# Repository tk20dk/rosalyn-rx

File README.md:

# rosalyn-rx
Rosalyn LoRa receiver

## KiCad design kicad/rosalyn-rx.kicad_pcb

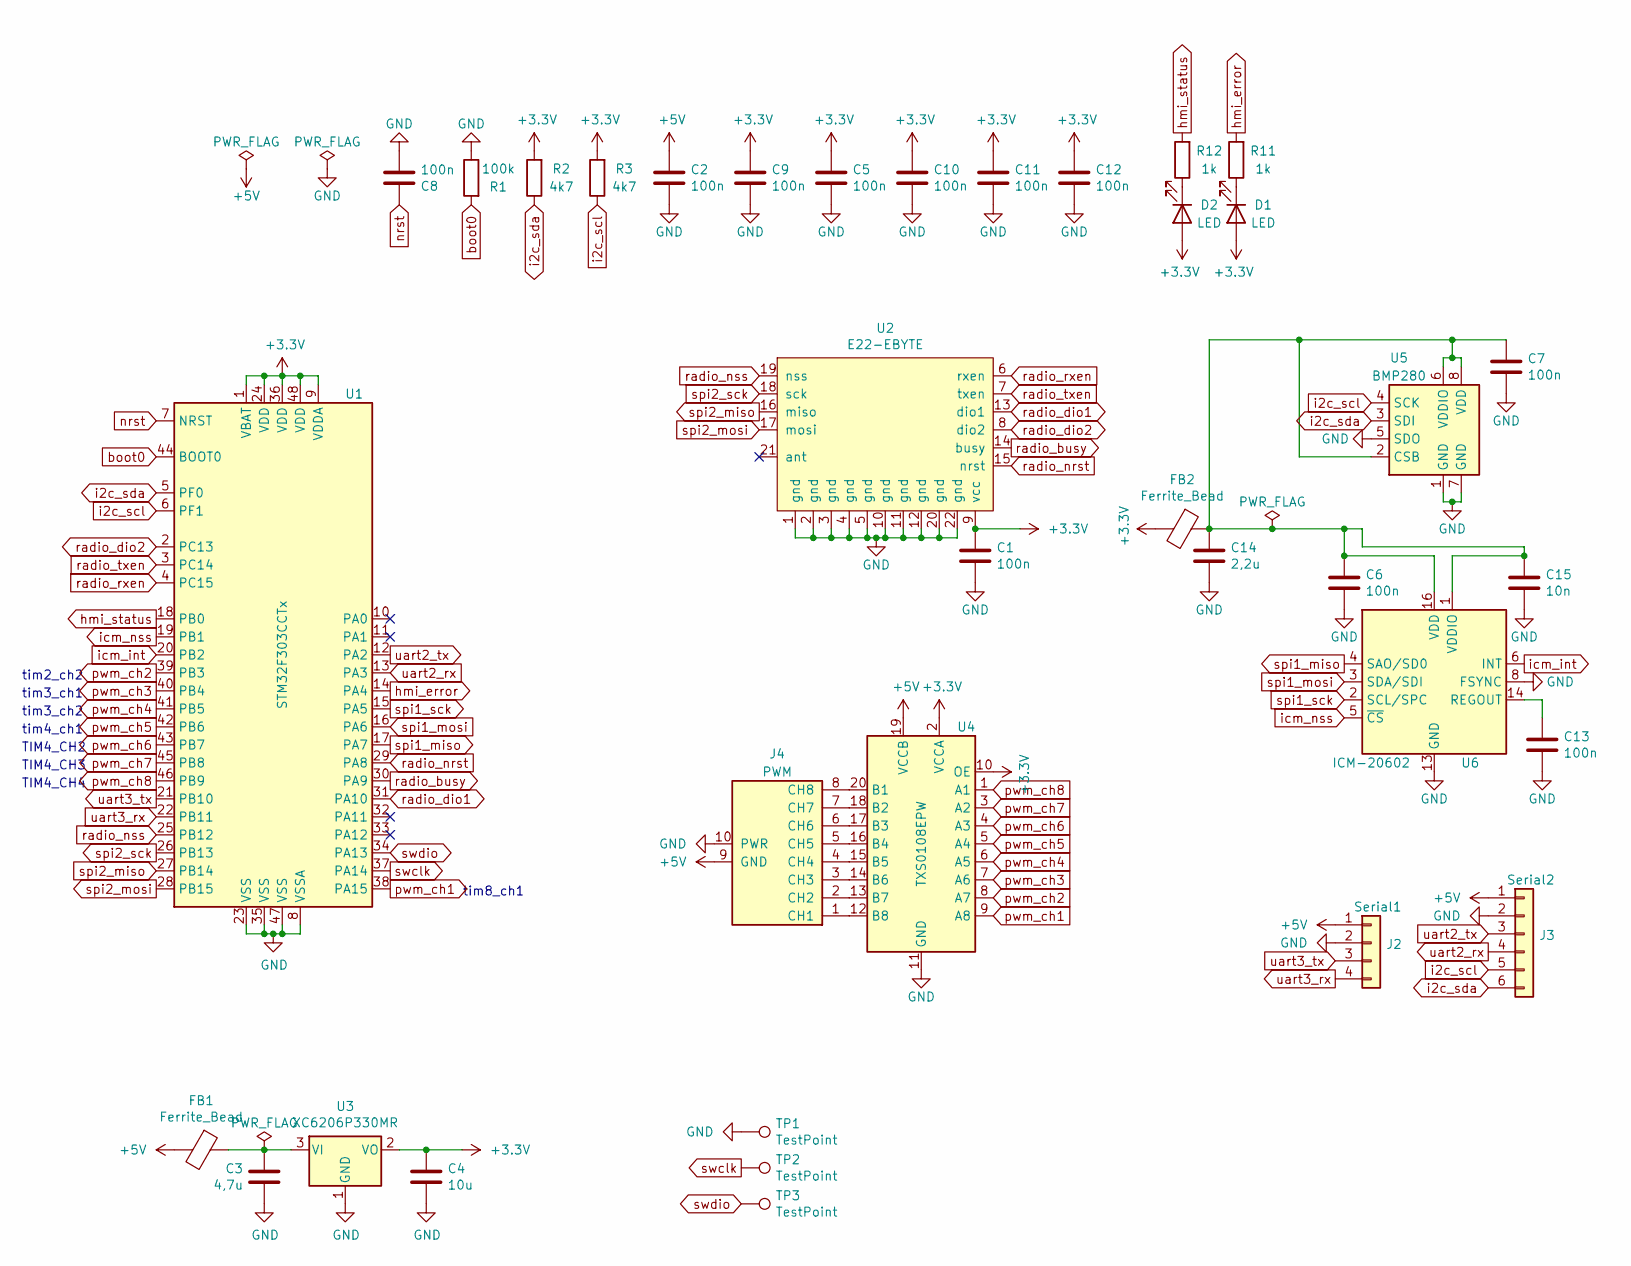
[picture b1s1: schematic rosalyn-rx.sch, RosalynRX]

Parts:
C1, C2, C5, C6, C7, C8, C9, C10, C11, C12, C13: 100n; C_0603_1608Metric
C3: 4,7u; C_0805_2012Metric
C4: 10u; C_0805_2012Metric
C14: 2,2u; C_0805_2012Metric
C15: 10n; C_0603_1608Metric
D1, D2: LED; LED_0603_1608Metric
FB1, FB2: Ferrite_Bead; L_0805_2012Metric
J2: Serial1; JST_SH_SM04B-SRSS-TB_1x04-1MP_P1.00mm_Horizontal
J3: Serial2; JST_SH_SM06B-SRSS-TB_1x06-1MP_P1.00mm_Horizontal
J4: PWM; PWM_3x08_P2.54mm_Vertical
R1: 100k; R_0603_1608Metric
R2, R3: 4k7; R_0603_1608Metric
R11, R12: 1k; R_0603_1608Metric
TP1, TP2, TP3: TestPoint; TestPoint_Pad_D1.0mm
U1: STM32F303CCTx; LQFP-48_7x7mm_P0.5mm
U2: E22-EBYTE
U3: XC6206P330MR; SOT-23
U4: TXS0108EPW; TSSOP-20_4.4x6.5mm_P0.65mm
U5: BMP280; Bosch_LGA-8_2x2.5mm_P0.65mm_ClockwisePinNumbering
U6: ICM-20602; LGA-16_3x3mm_P0.5mm_LayoutBorder3x5y

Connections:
+3V3: C1.1, C4.2, C5.1, C9.1, C10.1, C11.1, C12.1, D1.2 (A), D2.2 (A), FB2.2, R2.2, R3.2, U1.1 (VBAT), U1.9 (VDDA), U1.24 (VDD), U1.36 (VDD), U1.48 (VDD), U2.9 (vcc), U3.2 (VO), U4.2 (VCCA), U4.10 (OE)
+5V: C2.1, FB1.2, J2.1, J3.1, J4.9 (GND), U4.19 (VCCB)
GND: C1.2, C2.2, C3.1, C4.1, C5.2, C6.2, C7.2, C8.2, C9.2, C10.2, C11.2, C12.2, C13.2, C14.2, C15.2, J2.2, J3.2, J4.10 (PWR), R1.1, TP1.1, U1.8 (VSSA), U1.23 (VSS), U1.35 (VSS), U1.47 (VSS), U2.1 (gnd), U2.2 (gnd), U2.3 (gnd), U2.4 (gnd), U2.5 (gnd), U2.10 (gnd), U2.11 (gnd), U2.12 (gnd), U2.20 (gnd), U2.22 (gnd), U3.1 (GND), U4.11 (GND), U5.1 (GND), U5.5 (SDO), U5.7 (GND), U6.8 (FSYNC), U6.9 (GND), U6.10 (GND), U6.11 (GND), U6.12 (GND), U6.13 (GND), U6.15 (GND)
unnamed: C3.2, FB1.1, U3.3 (VI)
unnamed: C13.1, U6.14 (REGOUT)
unnamed: C6.1, C7.1, C14.1, C15.1, FB2.1, U5.2 (CSB), U5.6 (VDDIO), U5.8 (VDD), U6.1 (VDDIO), U6.16 (VDD)
unnamed: D1.1 (K), R11.1
unnamed: D2.1 (K), R12.1
unnamed: J4.1 (CH1), U4.12 (B8)
unnamed: J4.2 (CH2), U4.13 (B7)
unnamed: J4.3 (CH3), U4.14 (B6)
unnamed: J4.4 (CH4), U4.15 (B5)
unnamed: J4.5 (CH5), U4.16 (B4)
unnamed: J4.6 (CH6), U4.17 (B3)
unnamed: J4.7 (CH7), U4.18 (B2)
unnamed: J4.8 (CH8), U4.20 (B1)
boot0: R1.2, U1.44 (BOOT0)
hmi_error: R11.2, U1.14 (PA4)
hmi_status: R12.2, U1.18 (PB0)
i2c_scl: J3.5, R3.1, U1.6 (PF1), U5.4 (SCK)
i2c_sda: J3.6, R2.1, U1.5 (PF0), U5.3 (SDI)
icm_int: U1.20 (PB2), U6.6 (INT)
icm_nss: U1.19 (PB1), U6.5 (~CS)
nrst: C8.1, U1.7 (NRST)
pwm_ch1: U1.38 (PA15), U4.9 (A8)
pwm_ch2: U1.39 (PB3), U4.8 (A7)
pwm_ch3: U1.40 (PB4), U4.7 (A6)
pwm_ch4: U1.41 (PB5), U4.6 (A5)
pwm_ch5: U1.42 (PB6), U4.5 (A4)
pwm_ch6: U1.43 (PB7), U4.4 (A3)
pwm_ch7: U1.45 (PB8), U4.3 (A2)
pwm_ch8: U1.46 (PB9), U4.1 (A1)
radio_busy: U1.30 (PA9), U2.14 (busy)
radio_dio1: U1.31 (PA10), U2.13 (dio1)
radio_dio2: U1.2 (PC13), U2.8 (dio2)
radio_nrst: U1.29 (PA8), U2.15 (nrst)
radio_nss: U1.25 (PB12), U2.19 (nss)
radio_rxen: U1.4 (PC15), U2.6 (rxen)
radio_txen: U1.3 (PC14), U2.7 (txen)
spi1_miso: U1.17 (PA7), U6.4 (SAO/SD0)
spi1_mosi: U1.16 (PA6), U6.3 (SDA/SDI)
spi1_sck: U1.15 (PA5), U6.2 (SCL/SPC)
spi2_miso: U1.27 (PB14), U2.16 (miso)
spi2_mosi: U1.28 (PB15), U2.17 (mosi)
spi2_sck: U1.26 (PB13), U2.18 (sck)
swclk: TP2.1, U1.37 (PA14)
swdio: TP3.1, U1.34 (PA13)
uart2_rx: J3.4, U1.13 (PA3)
uart2_tx: J3.3, U1.12 (PA2)
uart3_rx: J2.4, U1.22 (PB11)
uart3_tx: J2.3, U1.21 (PB10)

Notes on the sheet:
tim8_ch1
tim2_ch2
tim3_ch1
tim3_ch2
tim4_ch1
TIM4_CH2
TIM4_CH3
TIM4_CH4

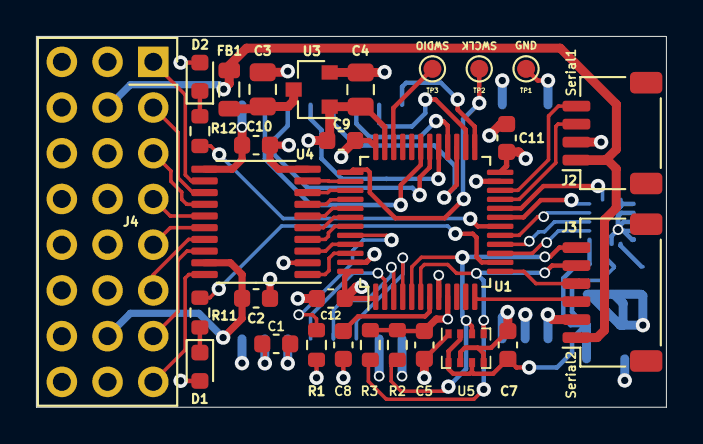
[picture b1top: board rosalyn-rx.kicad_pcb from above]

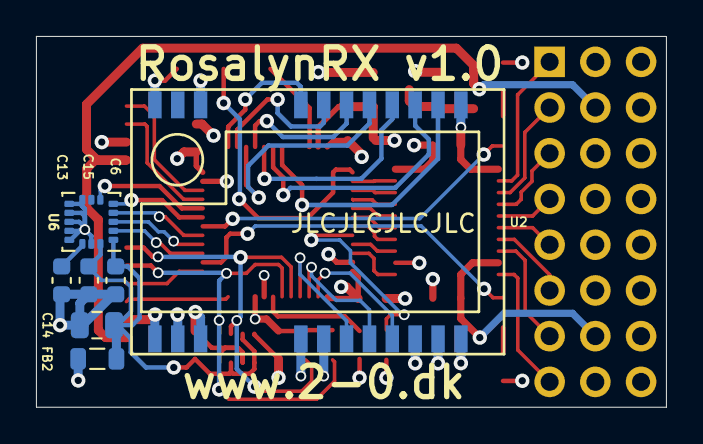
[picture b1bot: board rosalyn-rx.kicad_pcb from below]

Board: 4 copper layers, 35.0 x 20.6 mm, 36 parts (7 on the bottom side), 51 nets.

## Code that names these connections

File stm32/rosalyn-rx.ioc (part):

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Mcu.Name=STM32F072C(8-B)Tx
Mcu.Package=LQFP48
Mcu.UserName=STM32F072C8Tx
PA10.GPIOParameters=GPIO_PuPd,GPIO_Label
PA10.GPIO_Label=RADIO_DIO1
PA10.GPIO_PuPd=GPIO_NOPULL
PA10.Signal=GPXTI10
PA13.Mode=Serial_Wire
PA13.Signal=SYS_SWDIO
PA14.Mode=Serial_Wire
PA14.Signal=SYS_SWCLK
PA15.GPIOParameters=GPIO_Label
PA15.GPIO_Label=PWM_CH1
PA15.Signal=S_TIM2_CH1_ETR
PA2.Mode=Asynchronous
PA2.Signal=USART2_TX
PA3.GPIOParameters=GPIO_PuPd
PA3.GPIO_PuPd=GPIO_PULLUP
PA3.Mode=Asynchronous
PA3.Signal=USART2_RX
PA4.GPIOParameters=PinState,GPIO_Label
PA4.GPIO_Label=HMI_ERROR
PA4.PinState=GPIO_PIN_SET
PA4.Signal=GPIO_Output
PA5.Mode=Full_Duplex_Master
PA5.Signal=SPI1_SCK
PA6.GPIOParameters=GPIO_PuPd
PA6.GPIO_PuPd=GPIO_PULLUP
PA6.Mode=Full_Duplex_Master
PA6.Signal=SPI1_MISO
PA7.Mode=Full_Duplex_Master
PA7.Signal=SPI1_MOSI
PA8.GPIOParameters=PinState,GPIO_Label
PA8.GPIO_Label=RADIO_NRST
PA8.PinState=GPIO_PIN_SET
PA8.Signal=GPIO_Output
PA9.GPIOParameters=GPIO_PuPd,GPIO_Label
PA9.GPIO_Label=RADIO_BUSY
PA9.GPIO_PuPd=GPIO_NOPULL
PA9.Signal=GPIO_Input
PB0.GPIOParameters=PinState,GPIO_Label
PB0.GPIO_Label=HMI_STATUS
PB0.PinState=GPIO_PIN_SET
PB0.Signal=GPIO_Output
PB1.GPIOParameters=PinState,GPIO_Label
PB1.GPIO_Label=ICM_NSS
PB1.PinState=GPIO_PIN_SET
PB1.Signal=GPIO_Output
PB10.Mode=Asynchronous
PB10.Signal=USART3_TX
PB11.GPIOParameters=GPIO_PuPd
PB11.GPIO_PuPd=GPIO_PULLUP
PB11.Mode=Asynchronous
PB11.Signal=USART3_RX
PB12.GPIOParameters=PinState,GPIO_Label
PB12.GPIO_Label=RADIO_NSS
PB12.PinState=GPIO_PIN_SET
PB12.Signal=GPIO_Output
PB13.Mode=Full_Duplex_Master
PB13.Signal=SPI2_SCK
PB14.GPIOParameters=GPIO_PuPd
PB14.GPIO_PuPd=GPIO_PULLUP
PB14.Mode=Full_Duplex_Master
PB14.Signal=SPI2_MISO
PB15.Mode=Full_Duplex_Master
PB15.Signal=SPI2_MOSI
PB2.GPIOParameters=GPIO_PuPd,GPIO_Label
PB2.GPIO_Label=ICM_INT
PB2.GPIO_PuPd=GPIO_PULLDOWN
PB2.Signal=GPXTI2
PB3.GPIOParameters=GPIO_Label
PB3.GPIO_Label=PWM_CH2
PB3.Signal=S_TIM2_CH2
PB4.GPIOParameters=GPIO_Label
PB4.GPIO_Label=PWM_CH3
PB4.Signal=S_TIM3_CH1
PB5.GPIOParameters=GPIO_Label
PB5.GPIO_Label=PWM_CH4
PB5.Signal=S_TIM3_CH2
PB8.GPIOParameters=GPIO_Label
PB8.GPIO_Label=PWM_CH7
PB8.Signal=S_TIM16_CH1
PB9.GPIOParameters=GPIO_Label
PB9.GPIO_Label=PWM_CH8
PB9.Signal=S_TIM17_CH1
PC13.GPIOParameters=GPIO_PuPd,GPIO_Label
PC13.GPIO_Label=RADIO_DIO2
PC13.GPIO_PuPd=GPIO_NOPULL
PC13.Signal=GPIO_Input
PC14-OSC32_IN.GPIOParameters=GPIO_Label
PC14-OSC32_IN.GPIO_Label=RADIO_TXEN
PC14-OSC32_IN.Signal=GPIO_Output
PC15-OSC32_OUT.GPIOParameters=GPIO_Label
PC15-OSC32_OUT.GPIO_Label=RADIO_RXEN
PC15-OSC32_OUT.Signal=GPIO_Output
RCC.SYSCLKFreq_VALUE=48000000
RCC.SYSCLKSource=RCC_SYSCLKSOURCE_HSI48
board=custom

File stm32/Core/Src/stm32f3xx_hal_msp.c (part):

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
    __HAL_RCC_GPIOF_CLK_ENABLE();
    /**I2C2 GPIO Configuration
    PF0-OSC_IN     ------> I2C2_SDA
    PF1-OSC_OUT     ------> I2C2_SCL
    */
    GPIO_InitStruct.Pin = GPIO_PIN_0|GPIO_PIN_1;
    GPIO_InitStruct.Mode = GPIO_MODE_AF_OD;
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    __HAL_RCC_I2C2_CLK_DISABLE();

    /**I2C2 GPIO Configuration
    PF0-OSC_IN     ------> I2C2_SDA
    PF1-OSC_OUT     ------> I2C2_SCL
    */
    HAL_GPIO_DeInit(GPIOF, GPIO_PIN_0);

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
    __HAL_RCC_GPIOA_CLK_ENABLE();
    /**SPI1 GPIO Configuration
    PA5     ------> SPI1_SCK
    PA6     ------> SPI1_MISO
    PA7     ------> SPI1_MOSI
    */
    GPIO_InitStruct.Pin = GPIO_PIN_5|GPIO_PIN_6|GPIO_PIN_7;
    GPIO_InitStruct.Mode = GPIO_MODE_AF_PP;
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
    __HAL_RCC_GPIOB_CLK_ENABLE();
    /**SPI2 GPIO Configuration
    PB13     ------> SPI2_SCK
    PB14     ------> SPI2_MISO
    PB15     ------> SPI2_MOSI
    */
    GPIO_InitStruct.Pin = GPIO_PIN_13|GPIO_PIN_14|GPIO_PIN_15;
    GPIO_InitStruct.Mode = GPIO_MODE_AF_PP;
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    __HAL_RCC_SPI1_CLK_DISABLE();

    /**SPI1 GPIO Configuration
    PA5     ------> SPI1_SCK
    PA6     ------> SPI1_MISO
    PA7     ------> SPI1_MOSI
    */
    HAL_GPIO_DeInit(GPIOA, GPIO_PIN_5|GPIO_PIN_6|GPIO_PIN_7);

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    __HAL_RCC_SPI2_CLK_DISABLE();

    /**SPI2 GPIO Configuration
    PB13     ------> SPI2_SCK
    PB14     ------> SPI2_MISO
    PB15     ------> SPI2_MOSI
    */
    HAL_GPIO_DeInit(GPIOB, GPIO_PIN_13|GPIO_PIN_14|GPIO_PIN_15);

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  /* USER CODE END TIM2_MspPostInit 0 */
    __HAL_RCC_GPIOB_CLK_ENABLE();
    /**TIM2 GPIO Configuration
    PB3     ------> TIM2_CH2
    */
    GPIO_InitStruct.Pin = GPIO_PIN_3;
    GPIO_InitStruct.Mode = GPIO_MODE_AF_PP;
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
    __HAL_RCC_GPIOB_CLK_ENABLE();
    /**TIM3 GPIO Configuration
    PB4     ------> TIM3_CH1
    PB5     ------> TIM3_CH2
    */
    GPIO_InitStruct.Pin = GPIO_PIN_4|GPIO_PIN_5;
    GPIO_InitStruct.Mode = GPIO_MODE_AF_PP;
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
    __HAL_RCC_GPIOB_CLK_ENABLE();
    /**TIM4 GPIO Configuration
    PB6     ------> TIM4_CH1
    PB7     ------> TIM4_CH2
    PB8     ------> TIM4_CH3
    PB9     ------> TIM4_CH4
    */
    GPIO_InitStruct.Pin = GPIO_PIN_6|GPIO_PIN_7|GPIO_PIN_8|GPIO_PIN_9;
    GPIO_InitStruct.Mode = GPIO_MODE_AF_PP;
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
    __HAL_RCC_GPIOA_CLK_ENABLE();
    /**TIM8 GPIO Configuration
    PA15     ------> TIM8_CH1
    */
    GPIO_InitStruct.Pin = GPIO_PIN_15;
    GPIO_InitStruct.Mode = GPIO_MODE_AF_PP;
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
    __HAL_RCC_GPIOA_CLK_ENABLE();
    /**USART2 GPIO Configuration
    PA2     ------> USART2_TX
    PA3     ------> USART2_RX
    */
    GPIO_InitStruct.Pin = GPIO_PIN_2|GPIO_PIN_3;
    GPIO_InitStruct.Mode = GPIO_MODE_AF_PP;
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
    __HAL_RCC_GPIOB_CLK_ENABLE();
    /**USART3 GPIO Configuration
    PB10     ------> USART3_TX
    PB11     ------> USART3_RX
    */
    GPIO_InitStruct.Pin = GPIO_PIN_10|GPIO_PIN_11;
    GPIO_InitStruct.Mode = GPIO_MODE_AF_PP;
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    __HAL_RCC_USART2_CLK_DISABLE();

    /**USART2 GPIO Configuration
    PA2     ------> USART2_TX
    PA3     ------> USART2_RX
    */
    HAL_GPIO_DeInit(GPIOA, GPIO_PIN_2|GPIO_PIN_3);

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    __HAL_RCC_USART3_CLK_DISABLE();

    /**USART3 GPIO Configuration
    PB10     ------> USART3_TX
    PB11     ------> USART3_RX
    */
    HAL_GPIO_DeInit(GPIOB, GPIO_PIN_10|GPIO_PIN_11);

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
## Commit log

2020-11-19 created initial kicad and stm32 projects
2020-11-23 rosalyn-rx v1.0
2020-11-26 added nvdata driver
2020-11-26 updated nvdata driver
2020-12-10 pcb v1.0 - rx and tx is working
2020-12-10 added sbus and crypto support
2020-12-11 added pwm support for ch1 to ch4
2020-12-11 added pwm support for ch6 to ch7
2020-12-11 fixed radio to use SPI2
2020-12-13 TX to RX-PWM
2020-12-15 enabled TXCO to remove startup delay
2020-12-31 changed baudrate to 100000 8E2

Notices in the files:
stm32/Core/Src/stm32f3xx_hal_msp.c:
© Copyright (c) 2020 STMicroelectronics.
All rights reserved.
This software component is licensed by ST under BSD 3-Clause license,
the "License"; You may not use this file except in compliance with the
License. You may obtain a copy of the License at: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
(C) COPYRIGHT STMicroelectronics *****END OF FILE
